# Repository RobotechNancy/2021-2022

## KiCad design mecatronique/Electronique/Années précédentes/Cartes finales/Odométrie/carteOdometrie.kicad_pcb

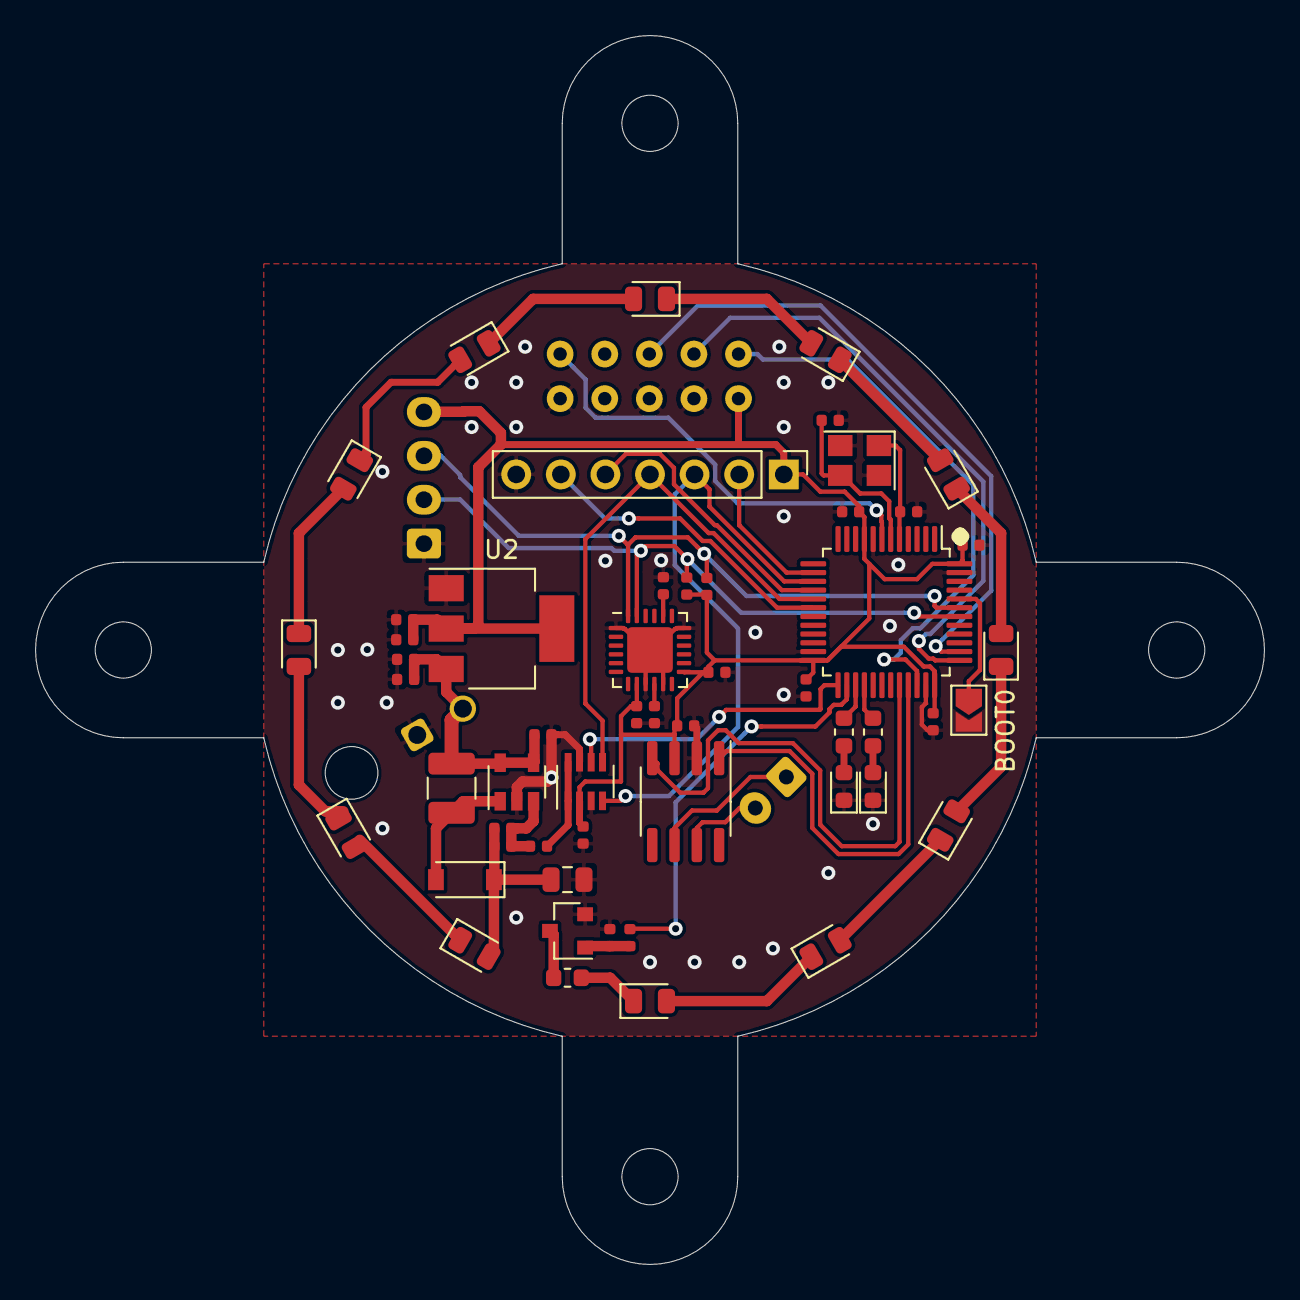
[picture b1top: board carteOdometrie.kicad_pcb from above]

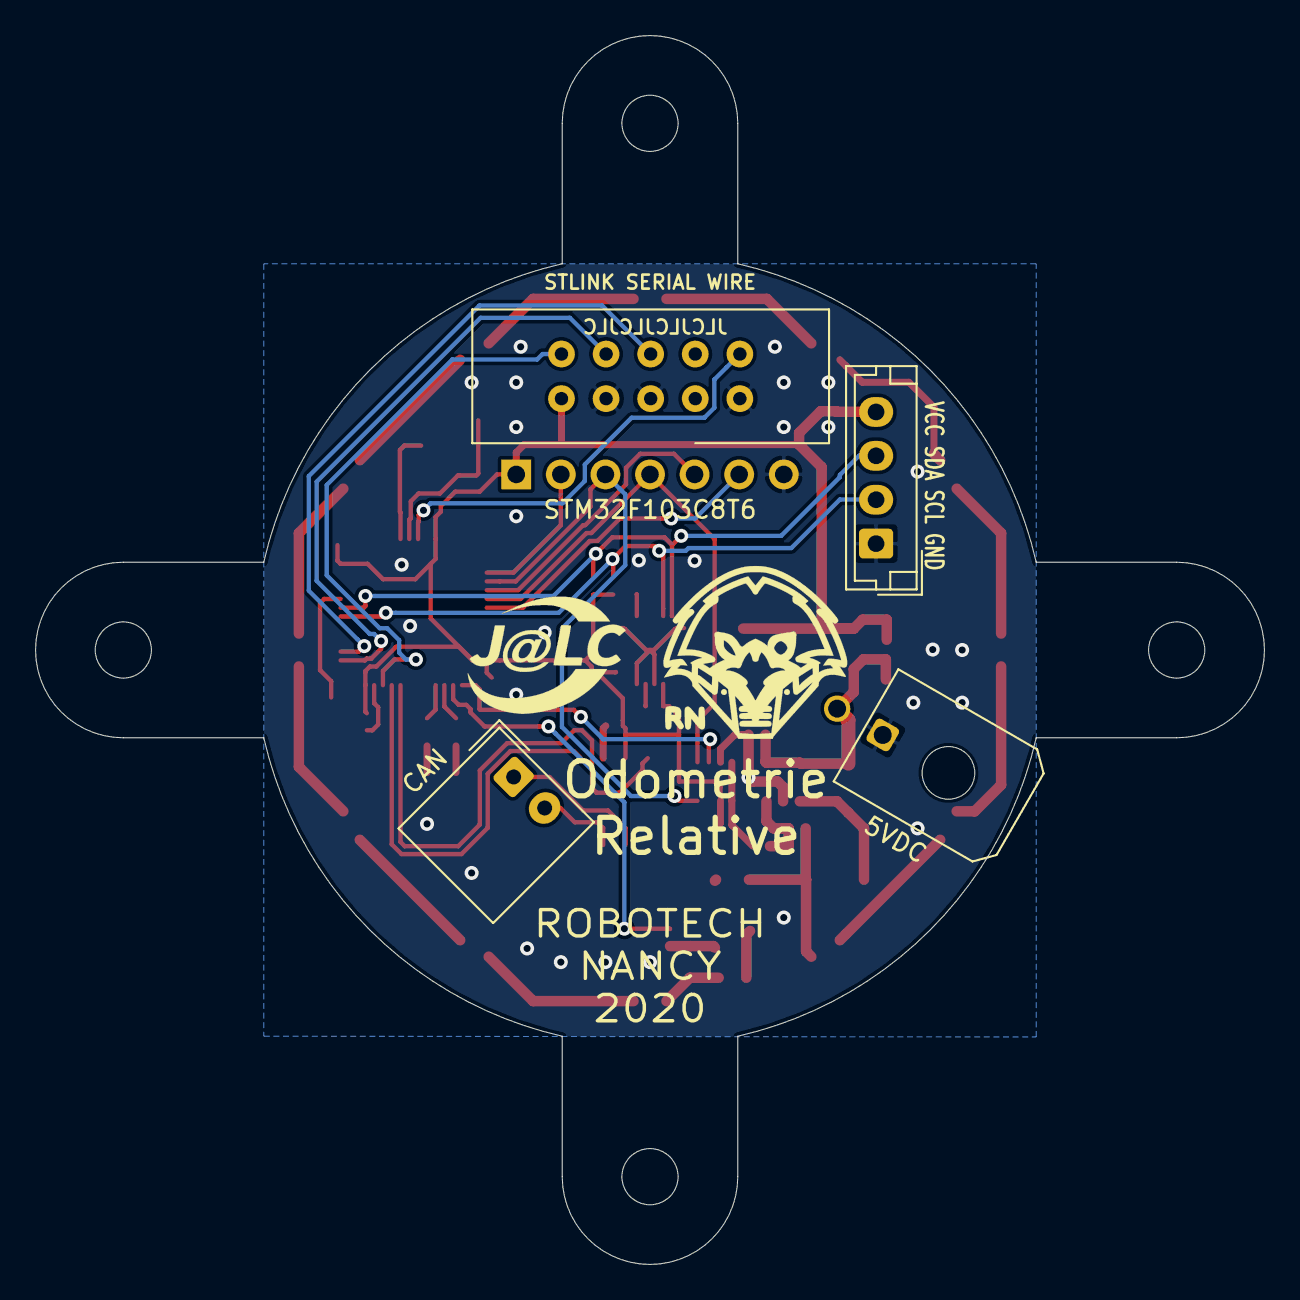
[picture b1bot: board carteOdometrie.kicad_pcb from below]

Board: 2 copper layers, 70.0 x 70.0 mm, 58 parts (4 on the bottom side), 47 nets.

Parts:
5VDC: Conn_01x02; Molex_Micro-Fit_3.0_43045-0200_2x01_P3.00mm_Horizontal
BOOT0: Jumper; SolderJumper-2_P1.3mm_Open_TrianglePad1.0x1.5mm
C1, C2: 22pF; C_0402_1005Metric
C3, C6, C7, C8, C9, C10, C11, C12, C15, C16, C17, C18: 10nF; C_0402_1005Metric
C4, C5, C19: 4.7uF; C_0402_1005Metric
C13: 0.1nF; C_0402_1005Metric
C14: 1uF; C_0805_2012Metric
CAN: Conn_01x02; Molex_SPOX_5268-02A_1x02_P2.50mm_Horizontal
D1, D2: LED; LED_0603_1608Metric
D3: B5819W; D_SOD-123
D4, D5, D6, D7, D8, D9, D10, D11, D12, D13, D14, D15: LED; LED_0805_2012Metric
J1: Conn_01x07; PinHeader_1x07_P2.54mm_Vertical
L1: LQH32CN100K33L; L_1210_3225Metric
Q1: 2N7002; SOT-23
R1, R2, R5: 100; R_0603_1608Metric
R3, R6: 10k; R_0402_1005Metric
R4, R7: 220k; R_0402_1005Metric
R8, R9: 2.2k; R_0402_1005Metric
STLINK SERIAL WIRE: STM32_SW; JTAG10
U1: STM32F103C8Tx; LQFP-48_7x7mm_P0.5mm
U2: LT1117-3.3; SOT-223-3_TabPin2
U3: TCAN337; SOIC-8_3.9x4.9mm_P1.27mm
U4: AD5160; SOT-23-8
U5: MPU6050; QFN-24-1EP_4x4mm_P0.5mm_EP2.6x2.6mm
U6: TPS61041DBV; SOT-23-5
VCC SDA SCL GND: Conn_01x04; JST_EH_B4B-EH-A_1x04_P2.50mm_Vertical
Y1: Crystal_GND24; Crystal_SMD_3225-4Pin_3.2x2.5mm

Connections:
+3V3: C5.1, C6.1, C7.1, C8.1, C9.1, C10.1, C11.1, C12.1, C15.1, C16.1, J1.1, R8.2, R9.2, STLINK SERIAL WIRE.1, U1.9, U1.24, U1.36, U1.48, U2.2, U3.3, U4.2, U5.8, U5.13, VCC SDA SCL GND.4
+5V: 5VDC.2, C3.1, C4.1, C19.1, L1.1, U2.3, U6.4, U6.5
/BOOT0: BOOT0.1, U1.44
/CAN_RX: U1.32, U3.4
/CAN_TX: U1.33, U3.1
/CLK: J1.3, U1.15, U4.4
/CSP: J1.2, U1.14
/CSR: U1.25, U4.6
/INT: J1.6, U1.18
/LED: R6.1, U1.26
/LEDG: R1.1, U1.28
/LEDY: R2.1, U1.27
/MISO: J1.5, U1.16
/MOSI: J1.4, U1.17, U4.5
/NRST: STLINK SERIAL WIRE.10, U1.7
/SCL: R9.1, U1.42, U5.23, VCC SDA SCL GND.2
/SDA: R8.1, U1.43, U5.24, VCC SDA SCL GND.3
/SWCLK: STLINK SERIAL WIRE.4, U1.37
/SWDIO: STLINK SERIAL WIRE.2, U1.34
/SWO: STLINK SERIAL WIRE.6, U1.38
GND: 5VDC.1, BOOT0.2, C1.1, C2.2, C3.2, C4.2, C5.2, C6.2, C7.2, C8.2, C9.2, C10.2, C11.2, C12.2, C14.2, C15.2, C16.2, C17.2, C18.2, C19.2, D1.1, D2.1, J1.7, Q1.2, R7.1, STLINK SERIAL WIRE.3, STLINK SERIAL WIRE.5, STLINK SERIAL WIRE.9, U1.8, U1.23, U1.35, U1.47, U2.1, U3.2, U4.3, U4.7, U5.1, U5.9, U5.11, U5.18, U6.2, VCC SDA SCL GND.1, Y1.2, Y1.4
unnamed: C1.2, U1.5, Y1.1
unnamed: C2.1, U1.6, Y1.3
unnamed: C13.1, C14.1, D3.1, D15.2, R4.2
unnamed: C13.2, R3.2, R4.1, U6.3
unnamed: C17.1, U5.20
unnamed: C18.1, U5.10
unnamed: CAN.1, U3.6
unnamed: CAN.2, U3.7
unnamed: D1.2, R1.2
unnamed: D2.2, R2.2
unnamed: D3.2, L1.2, U6.1
unnamed: D4.1, R5.1
unnamed: D4.2, D5.1
unnamed: D5.2, D6.1
unnamed: D6.2, D7.1
unnamed: D7.2, D8.1
unnamed: D8.2, D9.1
unnamed: D9.2, D10.1
unnamed: D10.2, D11.1
unnamed: D11.2, D12.1
unnamed: D12.2, D13.1
unnamed: D13.2, D14.1
unnamed: D14.2, D15.1
unnamed: Q1.1, R6.2, R7.2
unnamed: Q1.3, R5.2
unnamed: R3.1, U4.1, U4.8

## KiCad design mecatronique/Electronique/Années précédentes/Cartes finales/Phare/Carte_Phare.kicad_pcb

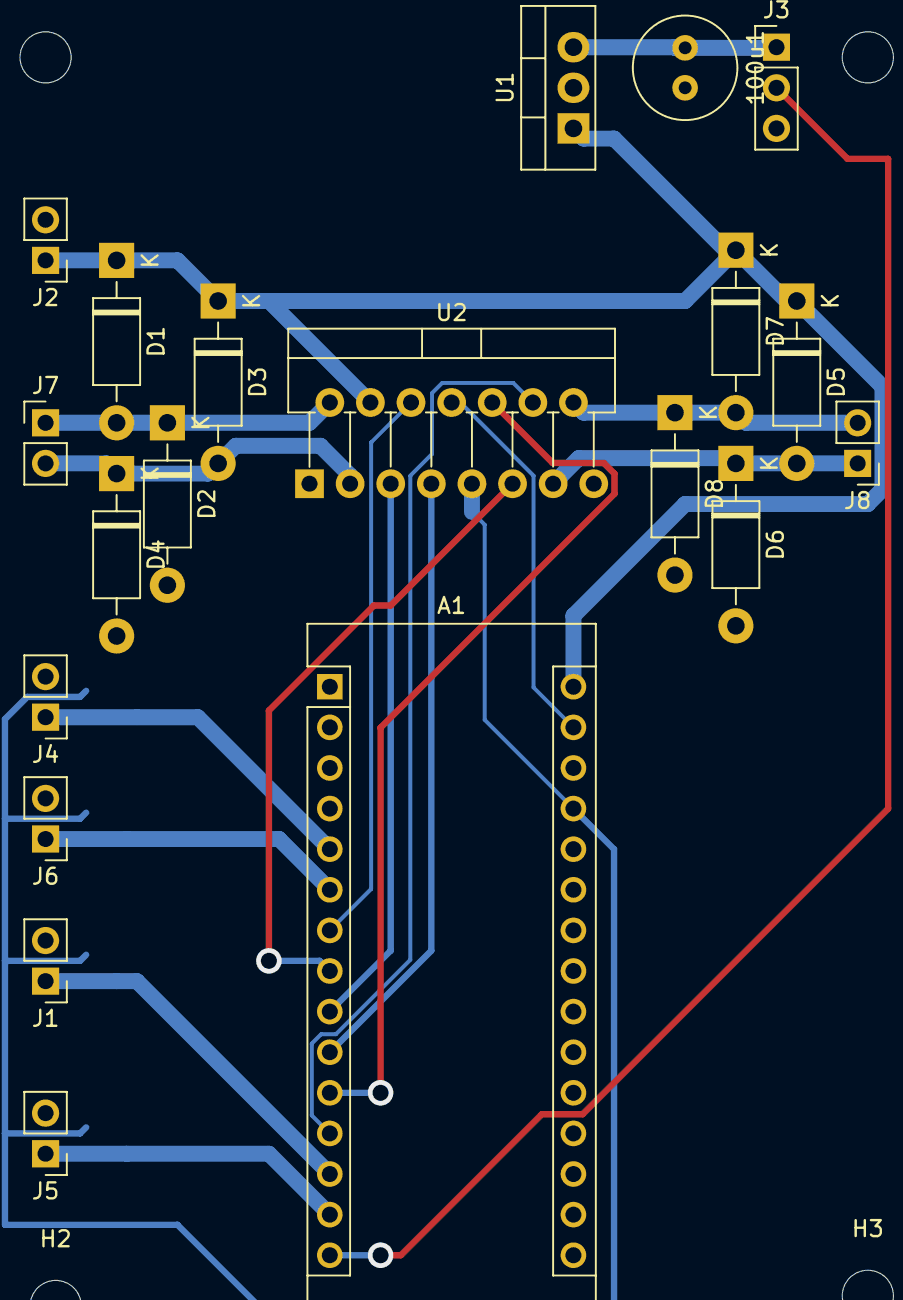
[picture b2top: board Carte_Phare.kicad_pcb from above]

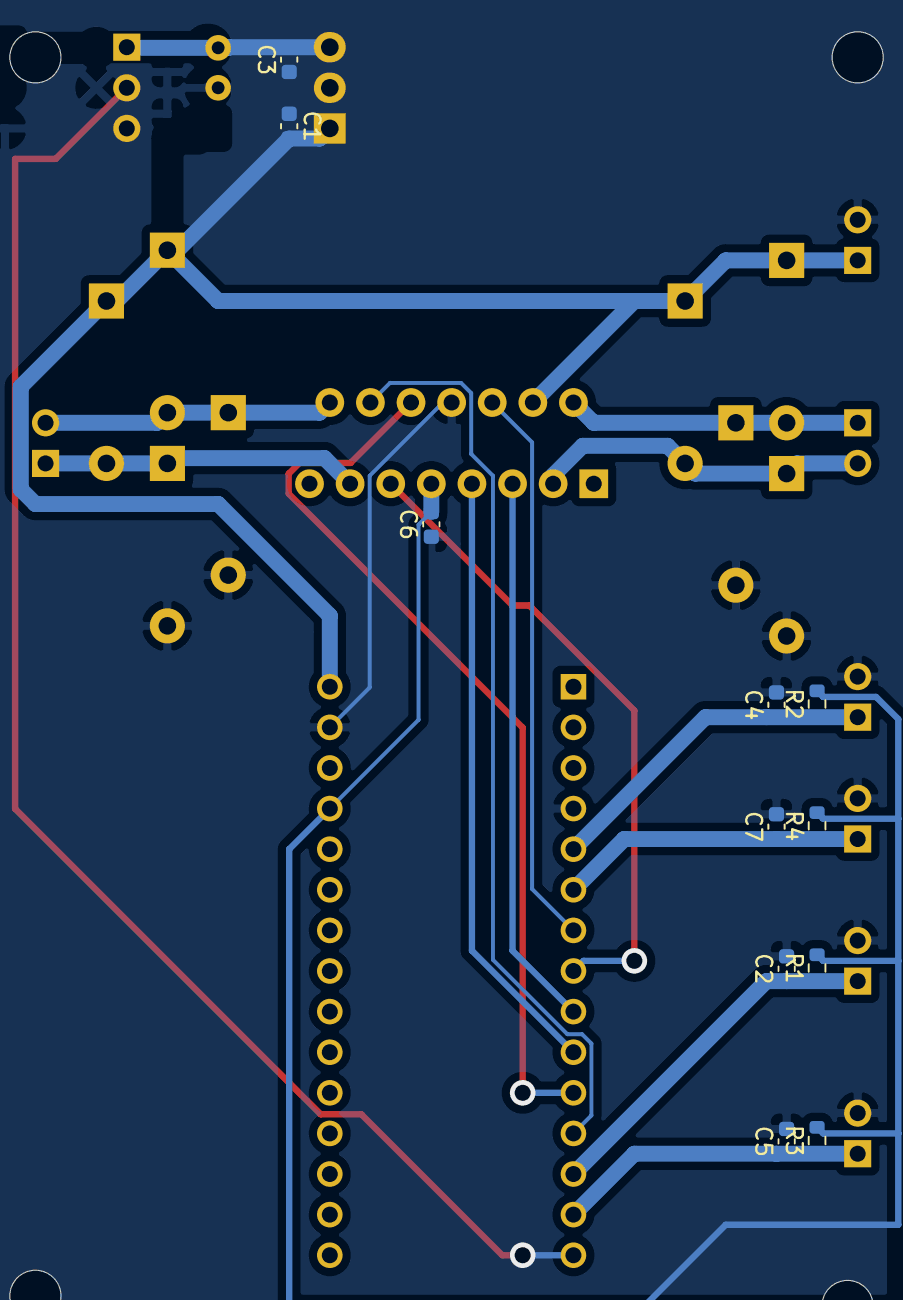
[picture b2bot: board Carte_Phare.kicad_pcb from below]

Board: 2 copper layers, 35 parts (11 on the bottom side), 19 nets.

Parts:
100u1: CP; C_Radial_D6.3mm_H11.0mm_P2.50mm
A1: Arduino_Nano_v3.x; Arduino_Nano
C1, C3: 100n; C_0603_1608Metric
C2, C4, C5, C7: C; C_0603_1608Metric
C6: 10nF; C_0603_1608Metric
D1, D2, D3, D4, D5, D6, D7, D8: 1N4004; D_DO-41_SOD81_P10.16mm_Horizontal
H1, H2, H3, H4: MountingHole_Pad; MountingHole_3.2mm_M3
J1, J2, J4, J5, J6, J7, J8: Conn_Batt; PinHeader_1x02_P2.54mm_Vertical
J3: Conn_01x03_Female; PinHeader_1x03_P2.54mm_Vertical
R1, R2, R3, R4: R; R_0603_1608Metric
U1: LM7805_TO220; TO-220-3_Vertical
U2: L298HN; TO-220-15_P2.54x2.54mm_StaggerOdd_Lead4.58mm_Vertical

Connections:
+5V: A1.27, C6.2, R1.2, R2.2, R3.2, R4.2, U2.9
+BATT: A1.30, C1.2, D1.1, D3.1, D5.1, D7.1, J2.1, U1.1, U2.4
/+_DC_MOTOR_Elevation: D1.2, D2.1, J7.1, U2.2
/+_DC_MOTOR_Supplementaire: D5.2, D6.1, J8.1, U2.13
/-_DC_MOTOR_Elevation: D3.2, D4.1, J7.2, U2.3
/-_DC_MOTOR_Supplementaire: D7.2, D8.1, J8.2, U2.14
/Conn_BoutonActivation: A1.13, C2.1, J1.1, R1.1
/Conn_BoutonDésactivation: A1.14, C5.1, J5.1, R3.1
/Conn_FinDeCourseBas: A1.6, C7.1, J6.1, R4.1
/Conn_FinDeCourseHaut: A1.5, C4.1, J4.1, R2.1
/Controle_LED: A1.15, J3.2
/L298_IN1: A1.9, U2.5
/L298_IN2: A1.10, U2.7
/L298_IN3: A1.11, U2.10
/L298_IN4: A1.12, U2.12
/L298_INA: A1.7, U2.6
/L298_INB: A1.8, U2.11
GND: 100u1.2, A1.4, A1.29, C1.1, C2.2, C3.1, C4.2, C5.2, C6.1, C7.2, D2.2, D4.2, D6.2, D8.2, H1.1, H2.1, H3.1, H4.1, J1.2, J2.2, J3.3, J4.2, J5.2, J6.2, U1.2, U2.8
VDD: 100u1.1, C3.2, J3.1, U1.3

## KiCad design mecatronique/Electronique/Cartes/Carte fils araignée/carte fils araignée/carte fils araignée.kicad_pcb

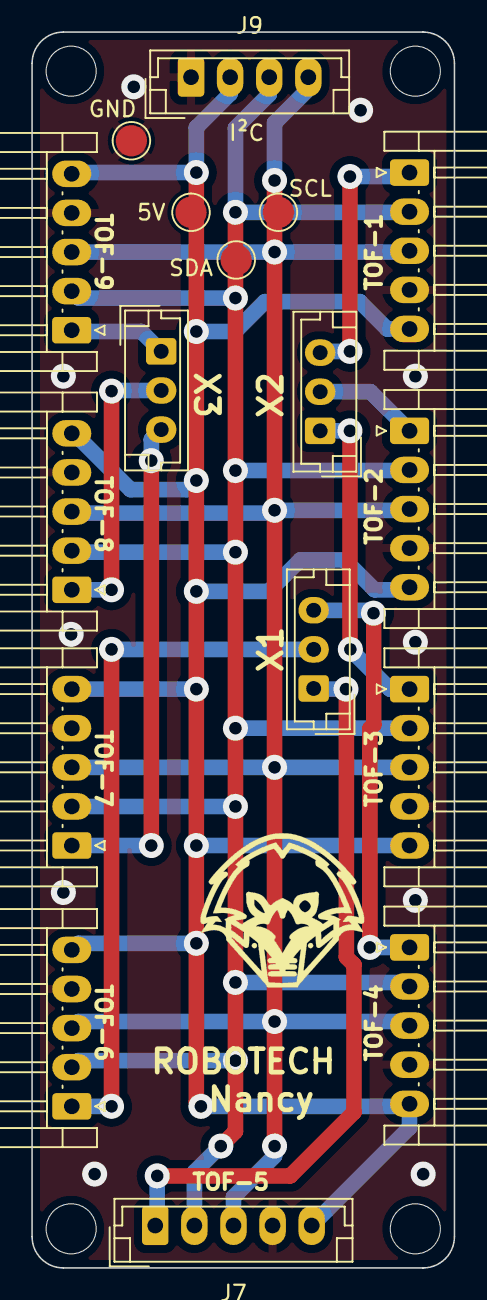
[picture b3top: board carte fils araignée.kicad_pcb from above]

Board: 2 copper layers, 27.0 x 79.0 mm, 17 parts (0 on the bottom side), 13 nets.

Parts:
+5V1: TestPoint; TestPoint_Pad_D2.0mm
GND1: TestPoint; TestPoint_Pad_D2.0mm
I2C_SCL1, I2C_SDA1: TestPoint; TestPoint_Pad_D2.0mm
J1, J2, J3, J4, J10, J11, J12, J13: Conn_01x05; JST_EH_S5B-EH_1x05_P2.50mm_Horizontal
J5: X3; JST_EH_B3B-EH-A_1x03_P2.50mm_Vertical
J6: X1; JST_EH_B3B-EH-A_1x03_P2.50mm_Vertical
J7: Conn_01x05; JST_EH_B5B-EH-A_1x05_P2.50mm_Vertical
J8: X2; JST_EH_B3B-EH-A_1x03_P2.50mm_Vertical
J9: Conn_01x04; JST_EH_B4B-EH-A_1x04_P2.50mm_Vertical

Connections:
+5V: +5V1.1, J1.5, J2.5, J3.5, J4.5, J7.5, J9.2, J10.5, J11.5, J12.5, J13.5
GND: GND1.1, J1.4, J2.4, J3.4, J4.4, J7.4, J9.1, J10.4, J11.4, J12.4, J13.4
I2C_SCL: I2C_SCL1.1, J1.3, J2.3, J3.3, J4.3, J7.3, J9.4, J10.3, J11.3, J12.3, J13.3
I2C_SDA: I2C_SDA1.1, J1.2, J2.2, J3.2, J4.2, J7.2, J9.3, J10.2, J11.2, J12.2, J13.2
Xshut1: J8.3, J10.1
Xshut2: J8.2, J11.1
Xshut3: J8.1, J12.1
Xshut4: J6.3, J13.1
Xshut5: J6.1, J7.1
Xshut6: J4.1, J6.2
Xshut7: J3.1, J5.3
Xshut8: J2.1, J5.2
Xshut9: J1.1, J5.1

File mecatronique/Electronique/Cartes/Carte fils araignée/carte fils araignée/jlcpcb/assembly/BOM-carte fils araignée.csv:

Comment,Designator,Footprint,LCSC
X3,J5,JST_EH_B3B-EH-A_1x03_P2.50mm_Vertical,
Conn_01x05,J2,JST_EH_S5B-EH_1x05_P2.50mm_Horizontal,
TestPoint,I2C_SCL1,TestPoint_Pad_D2.0mm,
Conn_01x05,J13,JST_EH_S5B-EH_1x05_P2.50mm_Horizontal,
Conn_01x05,J11,JST_EH_S5B-EH_1x05_P2.50mm_Horizontal,
Conn_01x05,J7,JST_EH_B5B-EH-A_1x05_P2.50mm_Vertical,
TestPoint,I2C_SDA1,TestPoint_Pad_D2.0mm,
Conn_01x05,J10,JST_EH_S5B-EH_1x05_P2.50mm_Horizontal,
TestPoint,GND1,TestPoint_Pad_D2.0mm,
Conn_01x05,J12,JST_EH_S5B-EH_1x05_P2.50mm_Horizontal,
X2,J8,JST_EH_B3B-EH-A_1x03_P2.50mm_Vertical,
X1,J6,JST_EH_B3B-EH-A_1x03_P2.50mm_Vertical,
Conn_01x05,J1,JST_EH_S5B-EH_1x05_P2.50mm_Horizontal,
Conn_01x04,J9,JST_EH_B4B-EH-A_1x04_P2.50mm_Vertical,
Conn_01x05,J4,JST_EH_S5B-EH_1x05_P2.50mm_Horizontal,
Conn_01x05,J3,JST_EH_S5B-EH_1x05_P2.50mm_Horizontal,
